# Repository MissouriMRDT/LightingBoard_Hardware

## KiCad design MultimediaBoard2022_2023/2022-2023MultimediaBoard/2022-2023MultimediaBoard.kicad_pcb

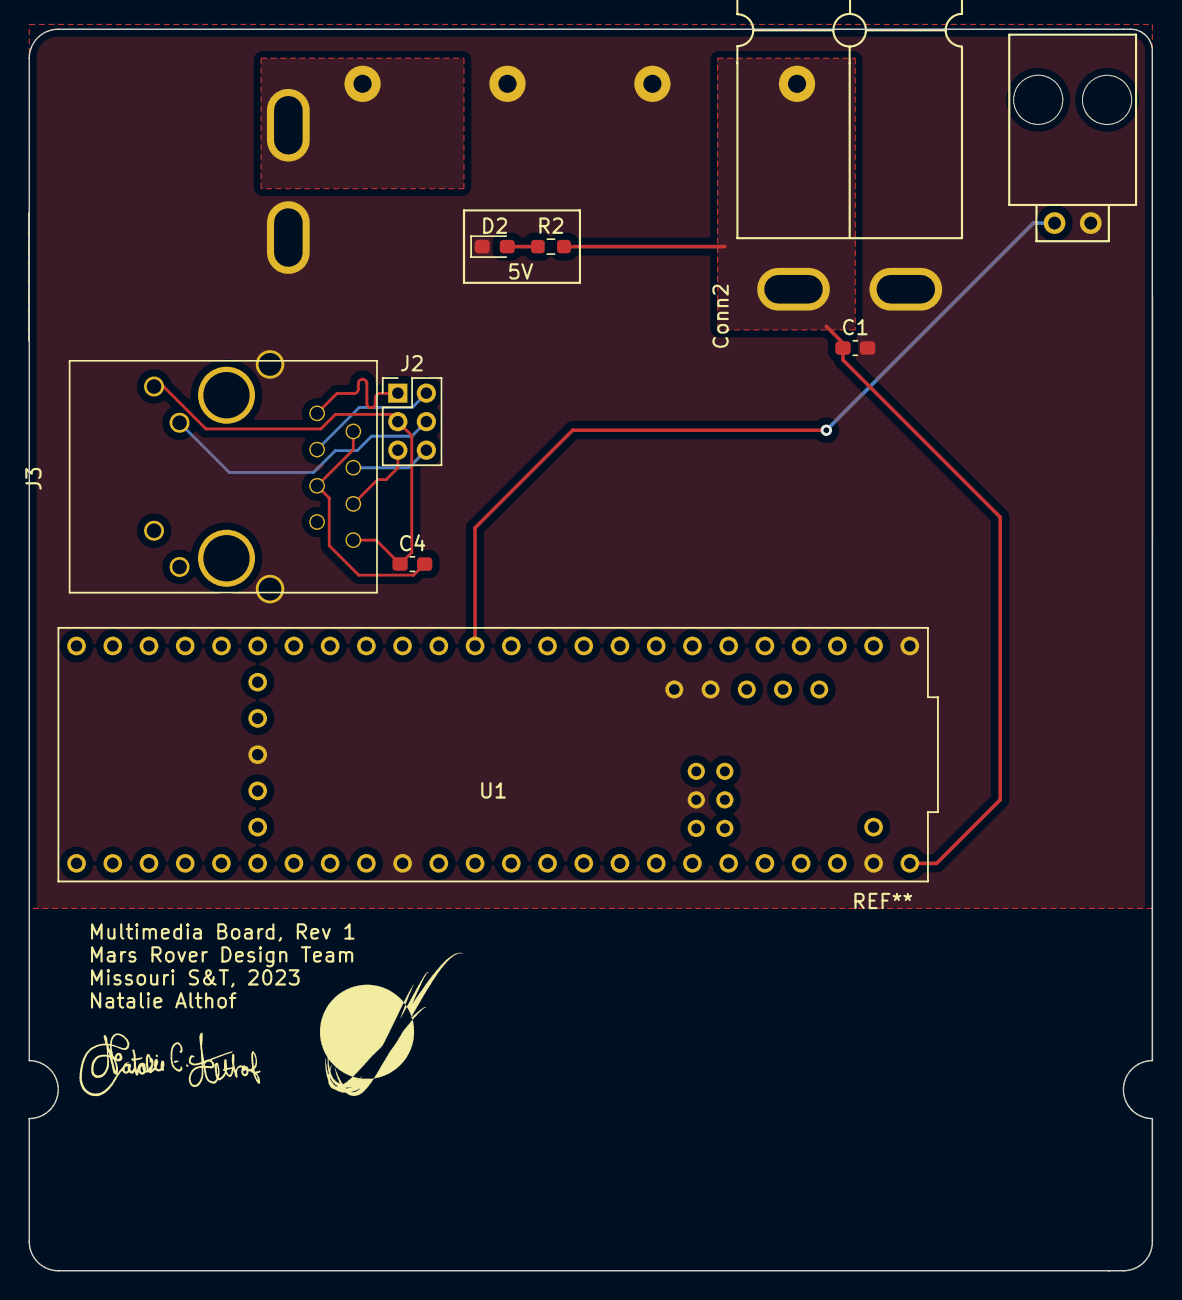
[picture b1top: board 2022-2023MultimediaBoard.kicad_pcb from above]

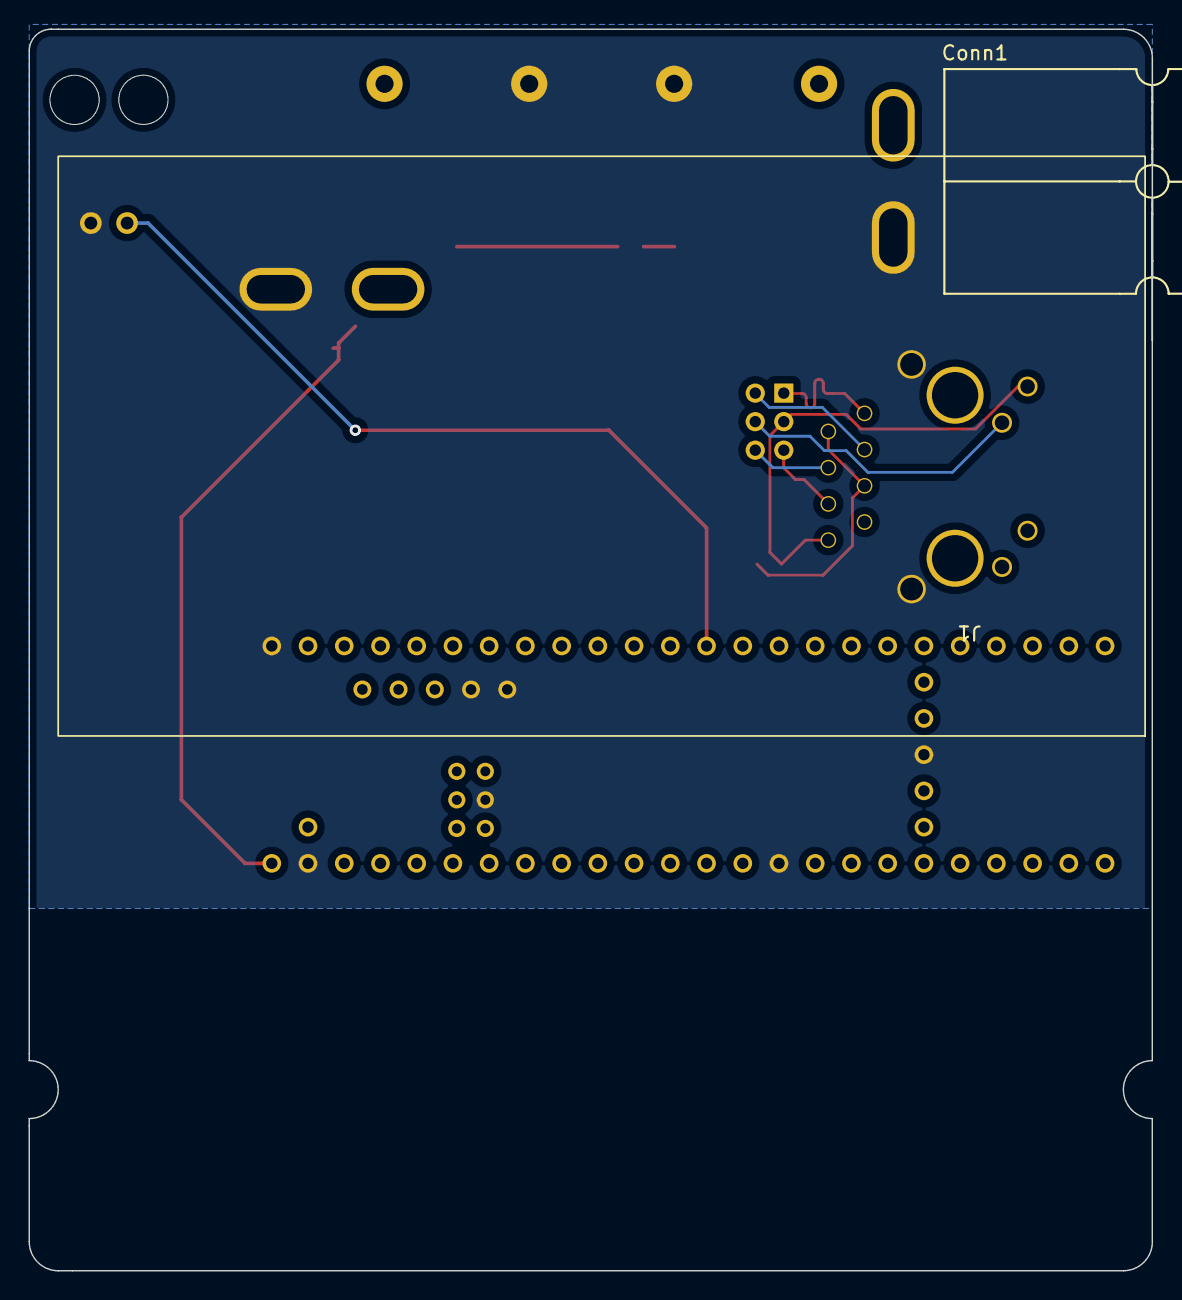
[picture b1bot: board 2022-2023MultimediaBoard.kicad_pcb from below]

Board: 2 copper layers, 78.7 x 87.0 mm, 11 parts (2 on the bottom side), 12 nets.

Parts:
C1, C4: 10uF; C_0603_1608Metric_Pad1.08x0.95mm_HandSolder
Conn1, Conn2: AndersonPP; Square_Anderson_2_H_Side_By_Side_PV
D2: GREEN; LED_0603_1608Metric_Pad1.05x0.95mm_HandSolder
J1: 5V 8A Buck Converter
J2: Conn_02x03_Counter_Clockwise; PinHeader_2x03_P2.00mm_Vertical
J3: RJ45_LED_Shielded_Ethernet; RJ45_Teensy
NeoPixelConn1: Molex_SL_02; MOLEX_SL_02_Horizontal
R2: 100; R_0603_1608Metric_Pad0.98x0.95mm_HandSolder
U1: Teensy4.1_DEV-16771; Teensy_4_1_Vertical

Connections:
+5V: C1.1, Conn2.4 (PV+), J1.4, R2.2, U1.VIN
+36V: Conn1.4 (PV+), J1.1
/Rx+: J2.6, J3.4
/Rx-: J2.5, J3.6
/Tx+: J2.1, J3.1
/Tx-: J2.2, J3.3
GND: C1.2, Conn1.1 (GND), Conn2.1 (GND), D2.1 (K), J1.2, J1.3, J3.SH, NeoPixelConn1.2, U1.GND1 (GND), U1.GND2 (GND), U1.GND3 (GND), U1.GND4 (GND), U1.GND5 (GND), U1.USB_GND1 (USB_GND), U1.USB_GND2 (USB_GND)
NeoPixels: NeoPixelConn1.1, U1.11 (MOSI)
unnamed: C4.1, J2.3, J3.8, J3.9
unnamed: C4.2, J3.2, J3.5
unnamed: D2.2 (A), R2.1
unnamed: J2.4, J3.10

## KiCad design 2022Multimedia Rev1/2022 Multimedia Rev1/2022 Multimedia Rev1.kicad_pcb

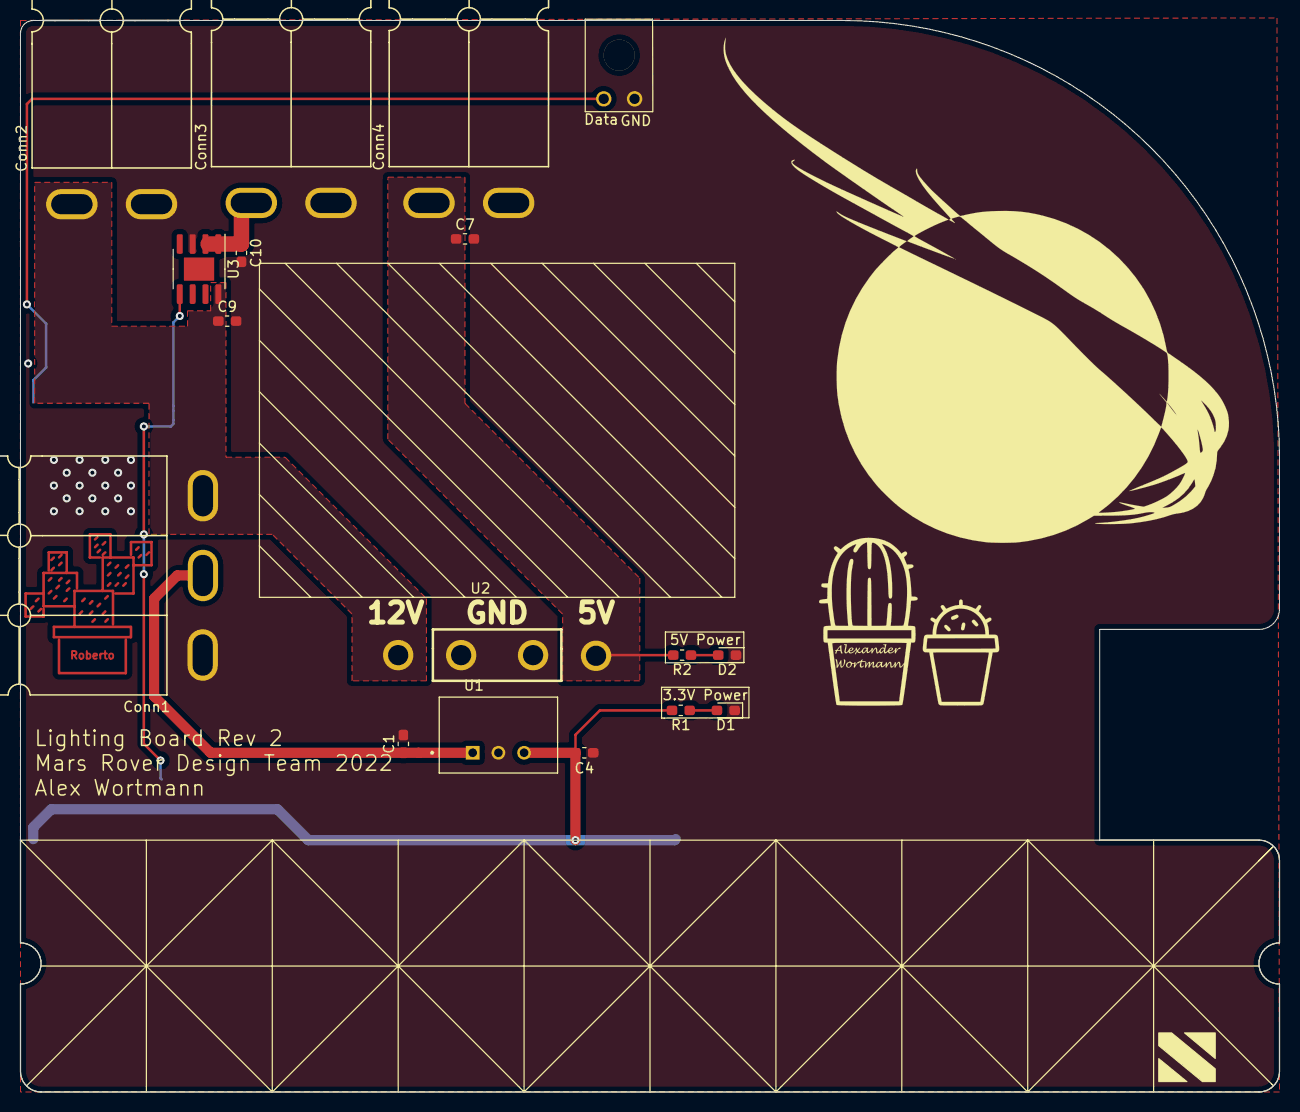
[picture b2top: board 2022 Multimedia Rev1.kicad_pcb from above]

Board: 2 copper layers, 124.5 x 105.9 mm, 18 parts (0 on the bottom side), 10 nets.

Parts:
C1, C4, C9, C10: 10 uF; C_0603_1608Metric_Pad1.05x0.95mm_HandSolder
C7: 10uF; C_0603_1608Metric_Pad1.05x0.95mm_HandSolder
Conn1: AndersonPP; Square_Anderson_3_H_Side_By_Side
Conn2: Wirrly Light; Square_Anderson_2_H_Side_By_Side
Conn3: Headlight; Square_Anderson_2_H_Side_By_Side
Conn4: AndersonPP; Square_Anderson_2_H_Side_By_Side
D1, D2: Green; D_0603_1608Metric_Pad1.05x0.95mm_HandSolder
Data: Neopixel Power; MOLEX_uF_S_02_Horizontal
R1: 120; R_0603_1608Metric_Pad1.05x0.95mm_HandSolder
R2: 300; R_0603_1608Metric_Pad1.05x0.95mm_HandSolder
U1: TSR1-2433; TSR_1-2433
U2: China5V8ABuck
U3: BDJ2GA5WEFJ; SOIC-8-1EP_3.9x4.9mm_P1.27mm_EP2.29x3mm
U4: TM4C129E_Launchpad; TM4C129E_Launchpad_FULL_SMD_BOTTOM

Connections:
+3V3: C4.1, R1.2, U1.3, U4.+3V3, U4.+3V3'
+5V: C7.1, Conn4.2, R2.2, U2.4
+12L: C1.1, Conn1.2, U1.1
+12VA: C9.1, Conn1.3, Conn2.2, U2.1, U3.8
AutopanelNeoPixel: Data.1, U4.PF1
GND: C1.2, C4.2, C7.2, C9.2, C10.2, Conn1.1, Conn2.1, Conn3.1, Conn4.1, D1.1, D2.1, Data.2, U1.2, U2.2, U2.3, U3.3, U4.GND
HeadlightToggle: U3.5, U4.PE3
unnamed: C10.1, Conn3.2, U3.1, U3.2
unnamed: D1.2, R1.1
unnamed: D2.2, R2.1

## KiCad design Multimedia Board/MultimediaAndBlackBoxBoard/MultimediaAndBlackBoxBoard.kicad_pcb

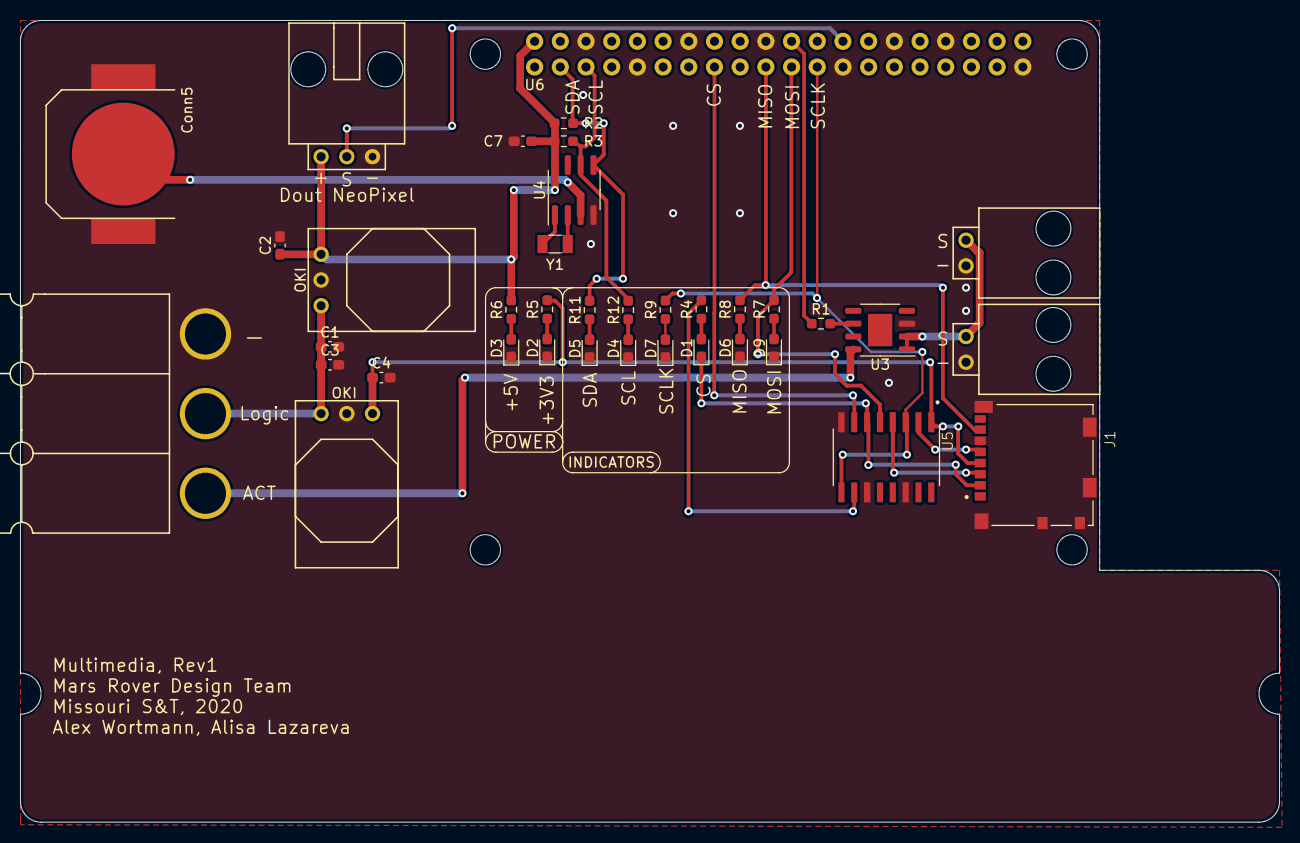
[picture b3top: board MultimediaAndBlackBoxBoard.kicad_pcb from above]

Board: 2 copper layers, 124.5 x 79.2 mm, 37 parts (0 on the bottom side), 30 nets.

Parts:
C1, C2, C3, C4, C7: 10uF; C_0603_1608Metric_Pad1.08x0.95mm_HandSolder
Conn1: Multimedia; Anderson_3_Horizontal_Side_by_Side
Conn2, Conn3: Molex_SL_02; MOLEX_SL_02_Horizontal
Conn4: Molex_SL_03; MOLEX_SL_03_Horizontal
Conn5: 12mm_Coin_Cell_Battery_Holder; CR1220_Battery_Holder
D1: SD_Select; LED_0603_1608Metric_Pad1.05x0.95mm_HandSolder
D2, D3: GREEN; LED_0603_1608Metric_Pad1.05x0.95mm_HandSolder
D4, D5, D6, D7, D9: BLUE; LED_0603_1608Metric_Pad1.05x0.95mm_HandSolder
J1: 104031-0811; MOLEX_104031-0811
R1, R6, R11, R12: 480; R_0603_1608Metric_Pad0.98x0.95mm_HandSolder
R2, R3: 1K; R_0603_1608Metric_Pad0.98x0.95mm_HandSolder
R4, R5, R7, R8, R9: 330; R_0603_1608Metric_Pad0.98x0.95mm_HandSolder
U1, U2: OKI; OKI_Horizontal
U3: BDJ2GA5WEFJ; HTSOP-8-1EP_3.9x4.9mm_P1.27mm_EP2.4x3.2mm
U4: DS1307Z+; SOIC-8_3.9x4.9mm_P1.27mm
U5: 4050; SOP127P780X200-16N
U6: Raspberry_Pi; RaspberryPi_THT_BOTTOM
Y1: 32.768KHz; Crystal_SMD_3215-2Pin_3.2x1.5mm

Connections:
+3V3: C4.1, J1.4, R5.2, U2.3, U5.1
+5V: C2.1, C7.1, Conn4.1, R2.1, R3.1, R6.2, U1.3, U4.8, U6.2
+5VA: Conn5.2, U4.3
+12V: C1.1, C3.1, Conn1.2, U1.1, U2.1
+12VA: Conn1.3, U3.8
Dout_NeoPixel: Conn4.2, U6.26
GND: C1.2, C2.2, C3.2, C4.2, C7.2, Conn1.1, Conn2.2, Conn3.2, Conn4.3, Conn5.1, D2.1, D3.1, D4.1, D5.1, D6.1, D7.1, D9.1, J1.6, J1.9, J1.10, J1.G1, J1.G2, J1.G3, J1.G4, U1.2, U2.2, U3.3, U4.4, U5.8, U5.11, U5.14, U6.6, U6.9, U6.14, U6.20, U6.25, U6.30, U6.34, U6.39
LightToggle: R1.1, U6.22
unnamed: Conn2.1, Conn3.1, U3.1, U3.2
unnamed: D1.1, J1.2, U5.6
unnamed: D1.2, R4.1
unnamed: D2.2, R5.1
unnamed: D3.2, R6.1
unnamed: D4.2, R12.1
unnamed: D5.2, R11.1
unnamed: D6.2, R8.1
unnamed: D7.2, R9.1
unnamed: D9.2, R7.1
unnamed: J1.3, U5.4
unnamed: J1.5, U5.2
unnamed: R1.2, U3.6
unnamed: R4.2, U5.10
unnamed: U4.1, Y1.2
unnamed: U4.2, Y1.1
SCL: R3.2, R12.2, U4.6, U6.5
SDA: R2.2, R11.2, U4.5, U6.3
SD_MISO: J1.7, R8.2, U6.19
SD_MOSI: R7.2, U5.5, U6.21
SD_SCLK: R9.2, U5.3, U5.9, U6.23
SD_Select: U5.7, U6.15

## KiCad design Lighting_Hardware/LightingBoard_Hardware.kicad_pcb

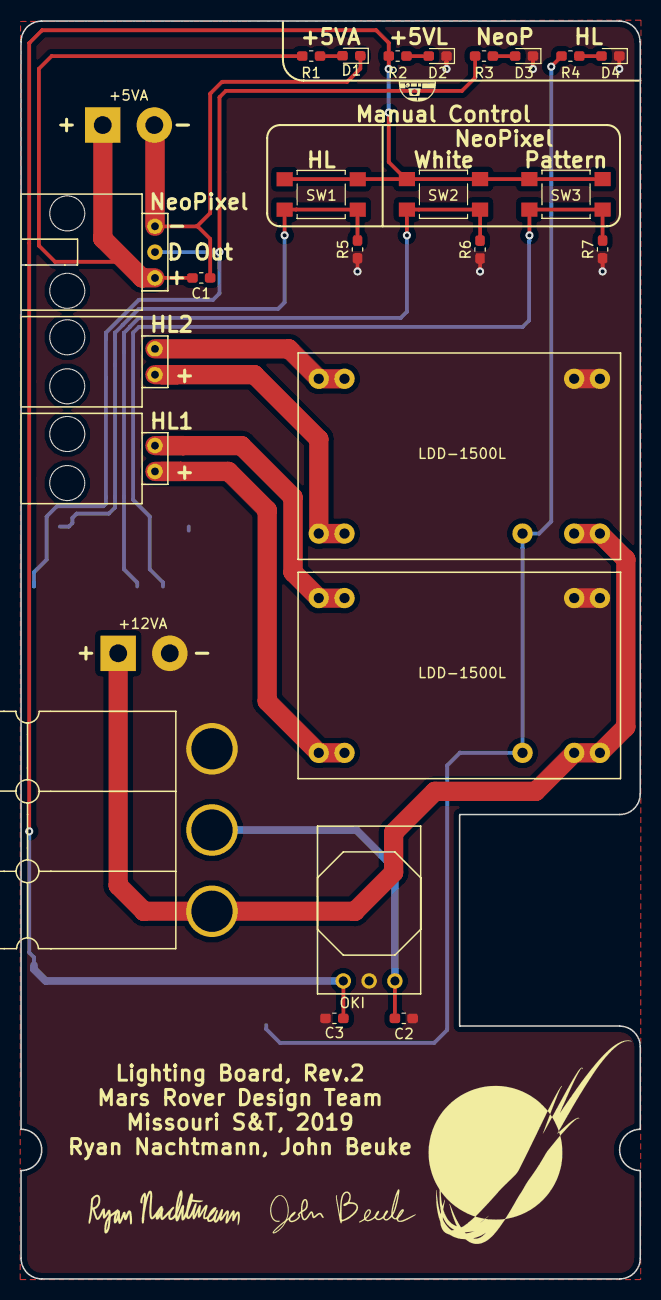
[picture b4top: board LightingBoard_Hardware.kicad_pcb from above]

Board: 2 copper layers, 61.0 x 123.8 mm, 27 parts (0 on the bottom side), 19 nets.

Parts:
+5VA, +12VA: SolderWirePad_1x02_P5.08mm_Drill1.5mm
C1, C2, C3: 10uF; C_0603_1608Metric_Pad1.05x0.95mm_HandSolder
Conn1: AndersonPP; Anderson_3_Horisontal_Side_by_Side
Conn2, Conn3: Molex_SL_02; MOLEX_SL_02_Horizontal
Conn4: Molex_SL_03; MOLEX_SL_03_Horizontal
D1, D2: G_LED; LED_0603_1608Metric_Pad1.05x0.95mm_HandSolder
D3, D4: Org_LED; LED_0603_1608Metric_Pad1.05x0.95mm_HandSolder
R1, R2, R3, R4: 500; R_0603_1608Metric_Pad1.05x0.95mm_HandSolder
R5, R6, R7: 10K; R_0603_1608Metric_Pad1.05x0.95mm_HandSolder
SW1, SW2, SW3: SW_Push; SW_SPST_TL3305A
U1, U2: LDD-1500L; LDD-1500L_LED_DRIVER
U3: TM4C129E_Launchpad; TM4C129E_Launchpad_X9_SMD_BOTTOM
U4: OKI; OKI_Horizontal

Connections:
+5VA: +5VA.1, C1.1, Conn4.1, R1.1
+5VL: C3.1, R2.1, SW1.1, SW2.1, SW3.1, U3.+5V, U4.3
+12VA: +12VA.1, Conn1.3, U1.23, U1.24, U2.23, U2.24
/Headlight_V1+: Conn2.1, U1.13, U1.14
/Headlight_V1-: Conn2.2, U1.11, U1.12
/Headlight_V2+: Conn3.1, U2.13, U2.14
/Headlight_V2-: Conn3.2, U2.11, U2.12
Dout_NeoPixel: Conn4.2, R3.1, U3.PF1
GND: +12VA.2, C2.2, C3.2, Conn1.1, D2.1, D3.1, D4.1, R5.1, R6.1, R7.1, U1.1, U1.2, U2.1, U2.2, U3.GND, U4.2
GNDA: +5VA.2, C1.2, Conn4.3, D1.1
Headlight_OnOff_PWM: R4.1, U1.21, U2.21, U3.PB3
Headlight_Power: R5.2, SW1.2, U3.PM3
NeoPixel_Pattern: R7.2, SW3.2, U3.PL5
NeoPixel_White: R6.2, SW2.2, U3.PL4
unnamed: C2.1, Conn1.2, U4.1
unnamed: D1.2, R1.2
unnamed: D2.2, R2.2
unnamed: D3.2, R3.2
unnamed: D4.2, R4.2

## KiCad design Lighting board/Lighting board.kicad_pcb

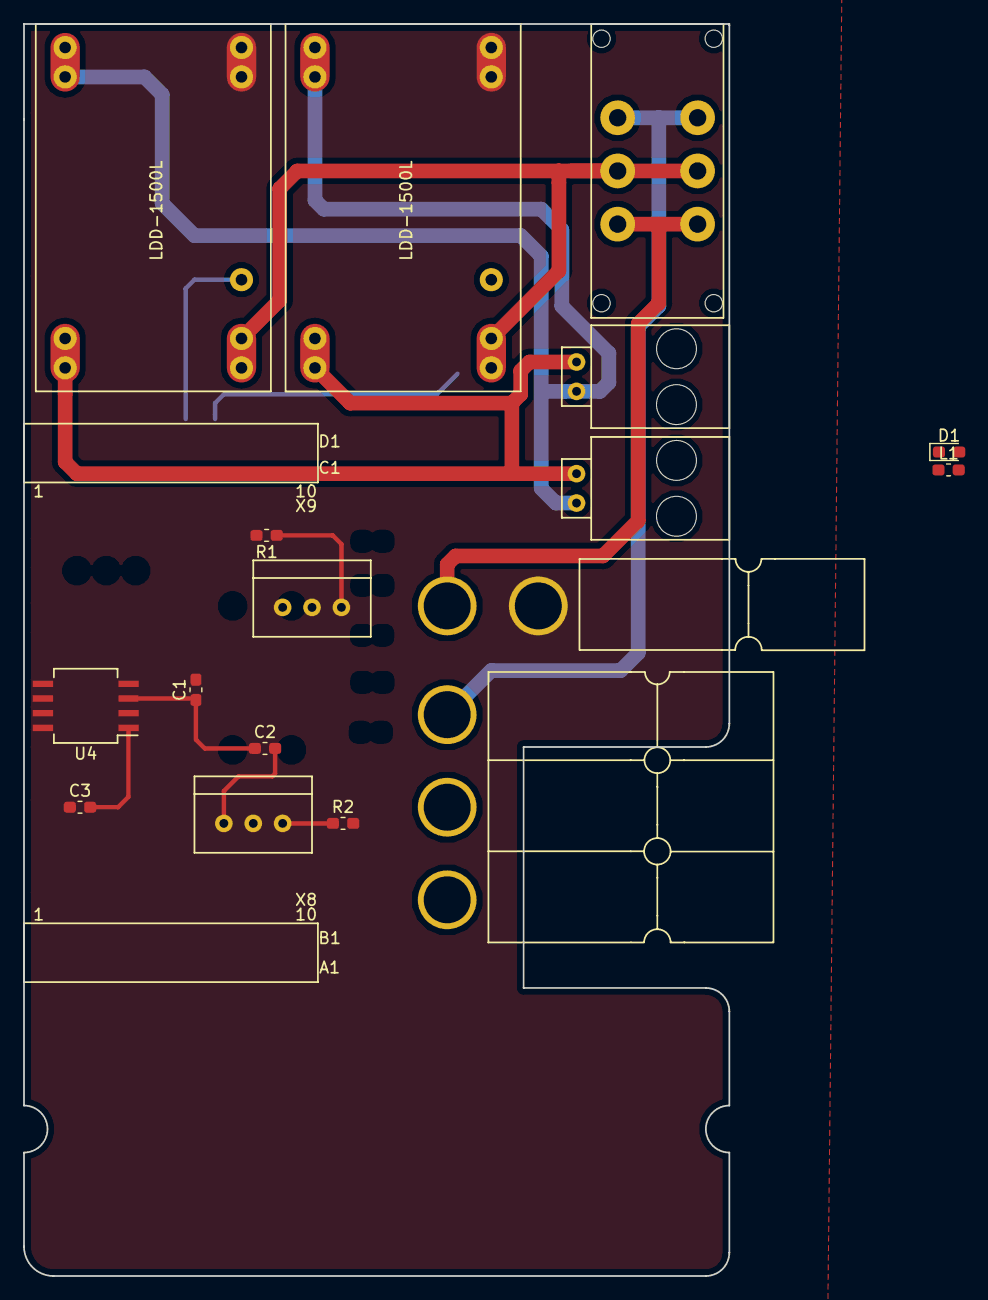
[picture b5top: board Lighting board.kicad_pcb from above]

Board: 2 copper layers, 61.0 x 108.2 mm, 18 parts (0 on the bottom side), 14 nets.

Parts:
C1, C2, C3: 10uF; C_0603_1608Metric_Pad1.05x0.95mm_HandSolder
Conn1: AndersonPP; Anderson_3_Horisontal_Side_by_Side
Conn1C1, Conn1D1: Molex_SL_02; MOLEX_SL_02_Horizontal
Conn2: AndersonPP; Anderson_2_Vertical
Conn2C1, Conn2C2: Molex_SL_03; MOLEX_SL_03_Vertical
D1: D_Schottky; D_0603_1608Metric_Pad1.05x0.95mm_HandSolder
L1: 47uH; L_0603_1608Metric_Pad1.05x0.95mm_HandSolder
R1, R2: 1k; R_0603_1608Metric_Pad1.05x0.95mm_HandSolder
SW1: SW_SPDT; 1P2T_Angled_Slide_GPI-152-3013
U1, U2: LDD-1500L; LDD-1500L_LED_DRIVER
U3: TM4C129E_Launchpad; TM4C129E_Launchpad_X9_Bottom_SMD
U4: AP1059; SO-8_5.3x6.2mm_P1.27mm

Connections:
5V: C1.1, C2.1, L1.2, U3.+5V, U4.3
/+12V: C3.2, Conn1.2, U4.1
/Headlight_V+: Conn1C1.1, Conn1D1.1, U1.8, U1.9, U2.8, U2.9
/Headlight_V-: Conn1C1.2, Conn1D1.2, U1.6, U1.7, U2.6, U2.7
Dout_NeoPixel1: R1.2, U3.PF1
GND: C2.2, C3.1, Conn1.1, Conn2.1, Conn2C1.2, Conn2C2.2, D1.2, U1.4, U1.5, U2.4, U2.5, U3.GND, U4.4, U4.5, U4.6, U4.7, U4.8
Headlight_OnOff_PWM1: U1.3, U3.PD0
Headlight_OnOff_PWM2: U2.3, U3.PD1
Headlight_Vin: SW1.2, U1.1, U1.2, U2.1, U2.2
unnamed: C1.2, Conn2C1.1
unnamed: Conn2C1.3, R1.1
unnamed: Conn2C2.3, R2.1
unnamed: D1.1, L1.1, U4.2
V+Act: Conn1.3, SW1.1

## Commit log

2018-10-14 Added Gitignore
2018-10-25 Initial Push
2018-10-25 Schematic/High Level Block Diagram
2018-10-26 PDR commit
2018-10-26 Final PDR commit
2018-11-03 Changes 11/3
    changed oki to AP1059 and started traces
2018-11-27 correct swithcing of the ap1509
2018-11-27 Create fp-lib-table
2018-12-10 Fixed Schematic
    Notes added for board review as well.
2018-12-16 Deleted duplicate file
2018-12-16 Fixed Schematic
2018-12-16 Fixed Scematic for the nth time
2018-12-16 BOM File creation
2018-12-16 PCB Layout Finished
2018-12-17 Traces are finished
2018-12-17 Fixed +5V plane
2018-12-17 Fixed polarity markers on the headlight molex to make it less confusing
2018-12-17 Fixed detached ground polygon
2018-12-17 Traces probably finished
2018-12-17 Probably finished the traces 2.0
2018-12-17 Added John's Signature
2018-12-19 Added BOM file
2018-12-19 Final Board
2018-12-19 Added Gerbs
2018-12-19 updated BOM
2018-12-19 Deleted old csv file
2018-12-19 made bom a csv
2018-12-19 Final update of the BOM
2018-12-19 changed BOM.txt to BOM.CSV
2018-12-19 Changed BOM.CSV.txt to BOM.CSV
2019-01-26 Clean up
    merged files from johns branch to master branch
2019-02-02 Cleaned up Branches
2019-02-23 Integrated push buttons
    neopixel- all white
    neopixel- pattern
    headlights-on/off
2019-02-23 Added push buttons
    cleaned up
2019-02-25 Rev2 Probably
2019-02-26 Rev2 Probably MK2
    Shifted the LDD-1500L's up by 1.5mm
2019-02-26 Rev2 Probably MK3
    Fixed a corrupted file or something of the sort
2019-03-01 Rev2 Probably MK4
2019-03-05 Added the NEW DC-DC Buck Converter for the NeoPixels
2019-03-05 Finished Rev2
2019-03-05 Regenerated Gerbs
2019-03-07 Created BOM Rev 2 and orgainzed documentation folder
    yeet
2020-10-21 Schematic start
2020-11-03 setup TIVA, 3.3V, 5V, Aux sections
2020-11-09 Added BlackBoxBoard to Multimedia
    seperated actuation and logic inputs and bucks, put multimedia board and black box board into heirarchal sheets as well as a raspberry pi, deleted tiva.
2020-11-29 Multimedia and Black Box Board finished
    real time clock added, sd card circuit fixed, indicators for all pins added (blue bc pink out of stock everywhere), etc
2020-11-29 layout started
    most components placed, battery cell wont cooperate (nets arent right)
2020-11-29 deleted ugly traces, added nice pretty ones
2020-11-30 traces redone
2020-11-30 Finished layout
2020-11-30 Finished Board
2020-11-30 Finalized Board
2020-11-30 SCLK added for SPI, tags renamed appropriately
2020-12-01 silkscreen finished
2020-12-15 gerbs created, BOM started
    board has been confirmed, just need to get BOM done
2020-12-16 BOM finished
2021-01-05 BOM updated
2021-10-02 Started schematic
2021-10-03 neatened up schematic
2021-10-13 Added another neopixel
2021-11-14 Finished layout and silkscreens
2021-11-15 Changed andersons
2021-11-17 Bom created
2021-12-08 generated .STEP file
2022-02-22 updated pin assignments
2022-02-22 changed headlight buck circuit
2022-03-08 Rev2 Done
    Need to do Gerbs
2022-03-11 change oki to china buck
2022-03-14 Finished rev2
    gerbs and all, except bom
2022-04-27 Created BOM
2022-09-07 deleted old board
2022-09-07 Started 2023 Multimedia board. Added teensy, capacitors, and oki
2022-09-14 Added ethernet port, buck converters, and LEDs
2022-09-16 Added LEDs, buck converters, ethernet, and power connectors
2022-09-22 removed headlight components
2022-09-29 Separated parts of schematic, changed power sources, and added labels
2022-09-30 Sectioned parts of schematic, changed power sources, grounded LEDs
2022-10-01 Renamed buck converter, minor touchups
2022-10-01 schematic pdf
2022-10-18 Quick fixes, new BOM
2022-10-19 Basic pcb layout
2022-10-21 PCB edits and footprint assignment
2022-11-01 Signature, flipped teensy
2022-11-02 PCB Header
2022-11-02 Layout updates
2022-11-16 Consolidated layout and reorganized
2022-11-19 Smaller layout
2022-11-19 generated gerbs
2022-11-19 forgot to zip up gerbs
